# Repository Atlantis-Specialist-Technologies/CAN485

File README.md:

# CAN485
Repository for the Sparkfun AST-CAN485 Development Board

[*Sparkfun AST CAN485 Development Board*](https://www.sparkfun.com/products/14483 "CAN485 on Sparkfun")

# Repository Contents
Repository for the CAN485 Board

* **/Libraries** - Libraries
* **/Examples** - Example code
* **/Documentation** - Documentation
* **/Firmware** - Arduino boards source
* **/Hardware** - Eagle design files

# Documentation
* **/Hookup Guide** - [Hookup guide](https://learn.sparkfun.com/tutorials/ast-can485-hookup-guide) for the CAN485. This contains everything needed to get up and running.

# Licensing
This product is open source.

Refer to LICENSE.md for license information

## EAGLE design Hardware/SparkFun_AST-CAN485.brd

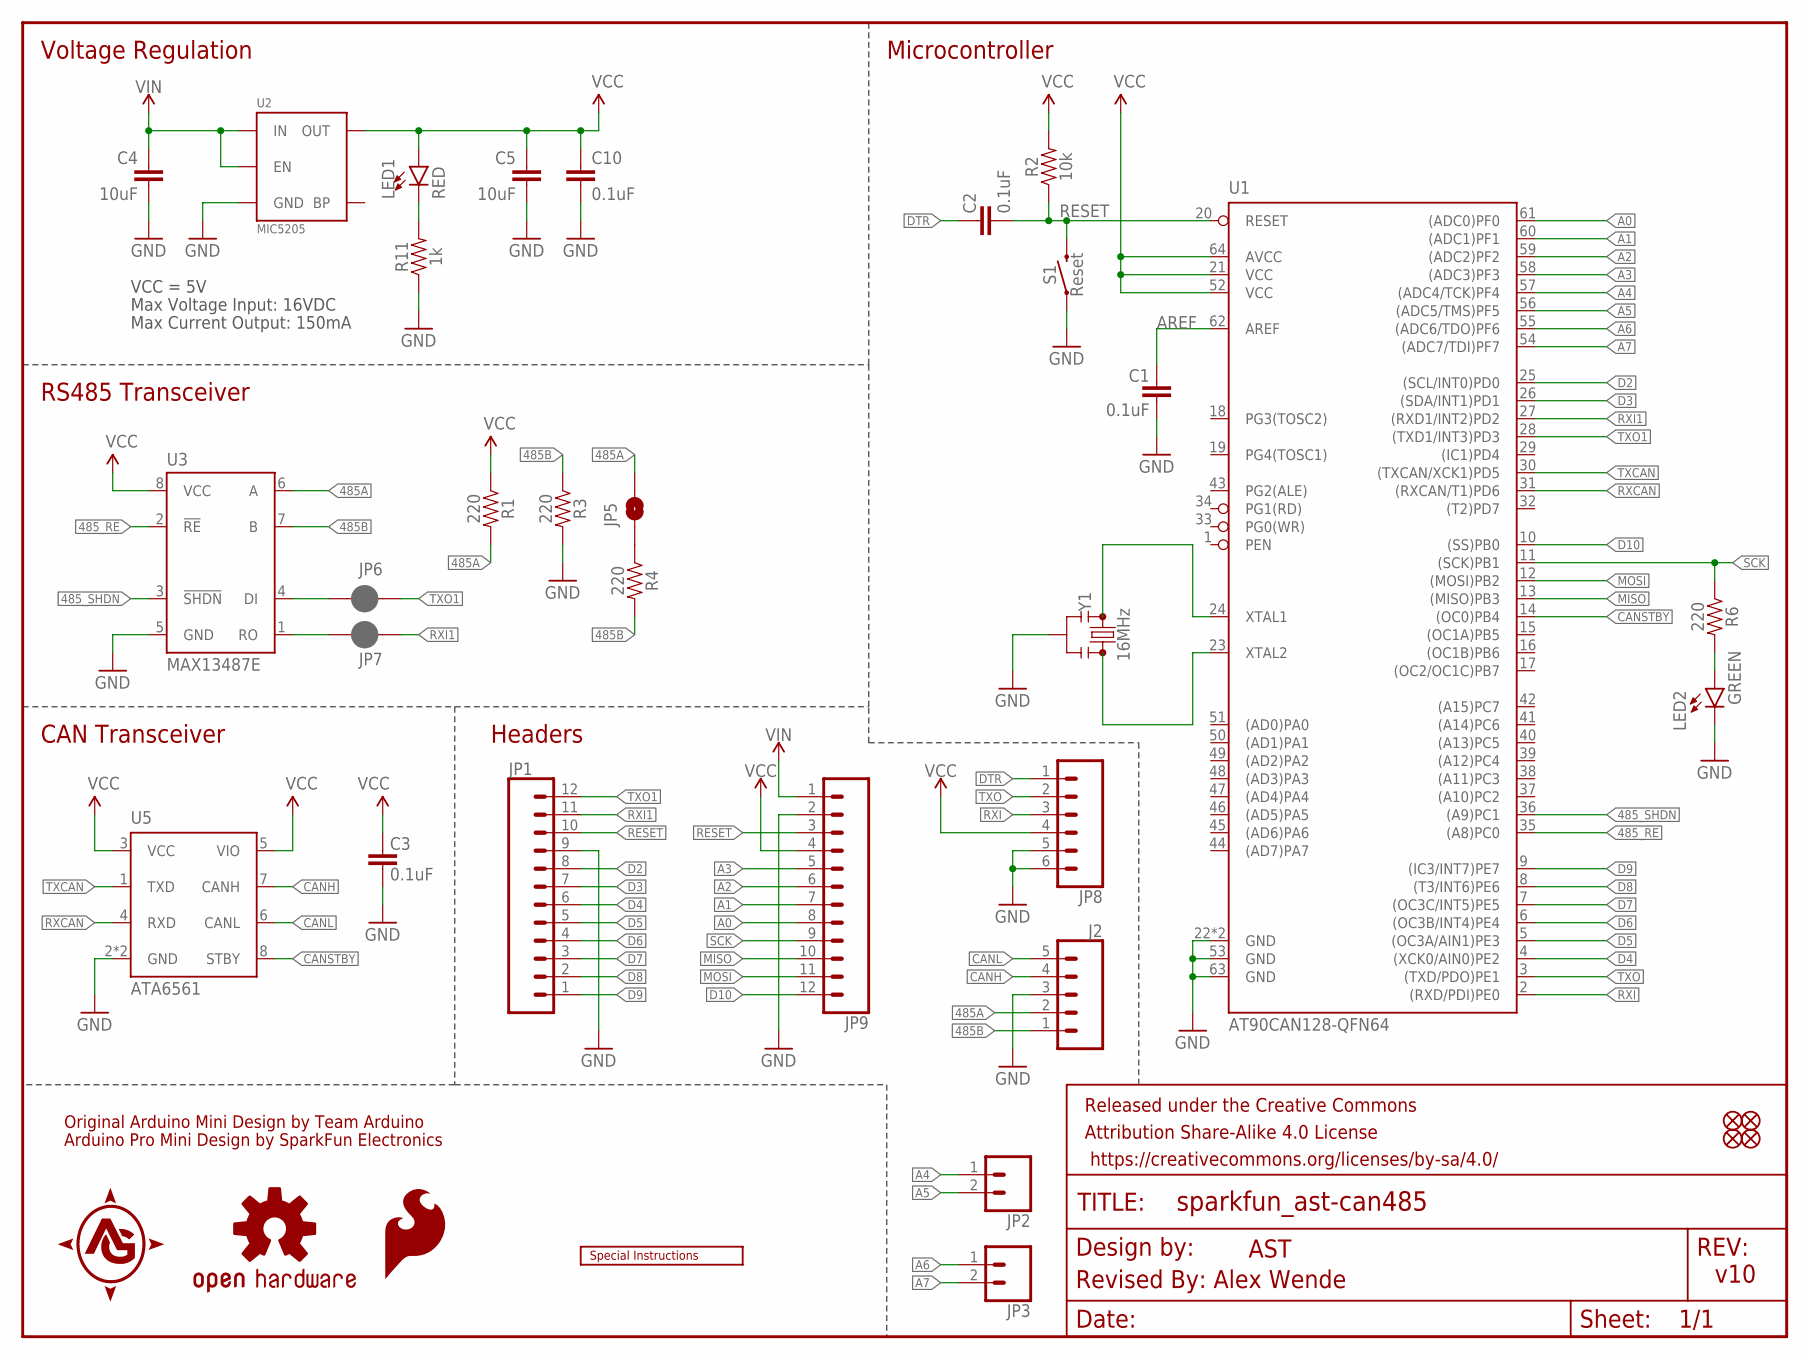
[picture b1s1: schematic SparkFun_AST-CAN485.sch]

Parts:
C1, C2, C3, C10: 0.1uF; 0402
C4, C5: 10uF; 1210
FD1, FD2, FD3, FD4: FIDUCIALUFIDUCIAL; FIDUCIAL-MICRO
FRAME1: FRAME-LETTER; CREATIVE_COMMONS
J2: CONN_05NO_SILK; 1X05_NO_SILK
JP1, JP9: CONN_12NO_SILK; 1X12_NO_SILK
JP2, JP3: CONN_021X02_NO_SILK; 1X02_NO_SILK
JP5: JUMPER-PAD-2-NO; PAD-JUMPER-2-NO_NO_SILK
JP6, JP7: JUMPER-SMT_2_NC_PASTE_NO-SILK; SMT-JUMPER_2_NC_PASTE_NO-SILK
JP8: CONN_06NO_SILK_NO_POP; 1X06_NO_SILK
LED1: RED; LED-0603
LED2: GREEN; LED-0603
LOGO1: OSHW-LOGOMINI; OSHW-LOGO-MINI
LOGO2: SFE_LOGO_FLAME0.05_INCH; SFE_LOGO_FLAME_.05
R1, R3, R4, R6: 220; 0603
R2: 10k; 0603
R11: 1k; 0603
S1: Reset; TACTILE_SWITCH_SMD_4.6X2.8MM
U1: AT90CAN128-QFN64; QFN-64
U2: MIC5205; SOT23-5
U3: MAX13487E; SO08
U5: ATA6561; DFN8
U$1: SPECIAL_INSTRUCTIONS-ORDERING; ORDERING_INSTRUCTIONS
Y1: 16MHz; RESONATOR-SMD-3.2X1.3(SLIM)

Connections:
485A: J2.2, JP5.2, R1.2, U3.6 (A)
485B: J2.1, R3.1, R4.2, U3.7 (B)
485_RE: U1.35 ((A8)PC0), U3.2 (!RE)
485_SHDN: U1.36 ((A9)PC1), U3.3 (!SHDN)
A0: JP9.8, U1.61 ((ADC0)PF0)
A1: JP9.7, U1.60 ((ADC1)PF1)
A2: JP9.6, U1.59 ((ADC2)PF2)
A3: JP9.5, U1.58 ((ADC3)PF3)
A4: JP2.1, U1.57 ((ADC4/TCK)PF4)
A5: JP2.2, U1.56 ((ADC5/TMS)PF5)
A6: JP3.1, U1.55 ((ADC6/TDO)PF6)
A7: JP3.2, U1.54 ((ADC7/TDI)PF7)
AREF: C1.2, U1.62 (AREF)
CANH: J2.4, U5.7 (CANH)
CANL: J2.5, U5.6 (CANL)
CANSTBY: U1.14 ((OC0)PB4), U5.8 (STBY)
D2: JP1.8, U1.25 ((SCL/INT0)PD0)
D3: JP1.7, U1.26 ((SDA/INT1)PD1)
D4: JP1.6, U1.4 ((XCK0/AIN0)PE2)
D5: JP1.5, U1.5 ((OC3A/AIN1)PE3)
D6: JP1.4, U1.6 ((OC3B/INT4)PE4)
D7: JP1.3, U1.7 ((OC3C/INT5)PE5)
D8: JP1.2, U1.8 ((T3/INT6)PE6)
D9: JP1.1, U1.9 ((IC3/INT7)PE7)
D10: JP9.12, U1.10 ((SS)PB0)
DTR: C2.2, JP8.1
GND: C1.1, C3.1, C4.2, C5.2, C10.2, J2.3, JP1.9, JP8.5, JP8.6, JP9.2, LED2.C, R3.2, R11.1, S1.1, S1.2 (1), U1.22 (GND), U1.53 (GND), U1.63 (GND), U1.65 (GND), U2.2 (GND), U3.5 (GND), U5.2 (GND), U5.9 (GND), Y1.2
MISO: JP9.10, U1.13 ((MISO)PB3)
MOSI: JP9.11, U1.12 ((MOSI)PB2)
unnamed: U1.23 (XTAL2), Y1.3
unnamed: U1.24 (XTAL1), Y1.1
unnamed: JP5.1, R4.1
unnamed: LED1.C, R11.2
unnamed: JP6.2, U3.4 (DI)
unnamed: JP7.2, U3.1 (RO)
unnamed: LED2.A, R6.2
RESET: C2.1, JP1.10, JP9.3, R2.1, S1.3 (2), S1.4 (2), U1.20 (RESET)
RXCAN: U1.31 ((RXCAN/T1)PD6), U5.4 (RXD)
RXI: JP8.3, U1.2 ((RXD/PDI)PE0)
RXI1: JP1.11, JP7.1, U1.27 ((RXD1/INT2)PD2)
SCK: JP9.9, R6.1, U1.11 ((SCK)PB1)
TXCAN: U1.30 ((TXCAN/XCK1)PD5), U5.1 (TXD)
TXO: JP8.2, U1.3 ((TXD/PDO)PE1)
TXO1: JP1.12, JP6.1, U1.28 ((TXD1/INT3)PD3)
VCC: C3.2, C5.1, C10.1, JP8.4, JP9.4, LED1.A, R1.1, R2.2, U1.21 (VCC), U1.52 (VCC), U1.64 (AVCC), U2.5 (OUT), U3.8 (VCC), U5.3 (VCC), U5.5 (VIO)
VIN: C4.1, JP9.1, U2.1 (IN), U2.3 (EN)

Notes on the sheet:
Original Arduino Mini Design by Team Arduino
Arduino Pro Mini Design by SparkFun Electronics
Max Voltage Input: 16VDC
Max Current Output: 150mA
VCC = 5V
Voltage Regulation
Microcontroller
RS485 Transceiver
CAN Transceiver
Headers
AST
Revised By: Alex Wende
v10

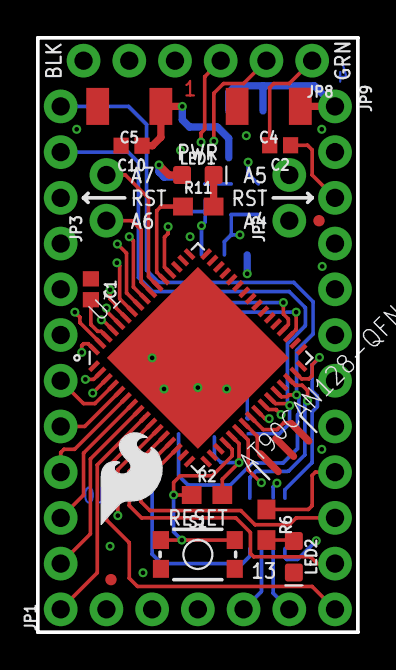
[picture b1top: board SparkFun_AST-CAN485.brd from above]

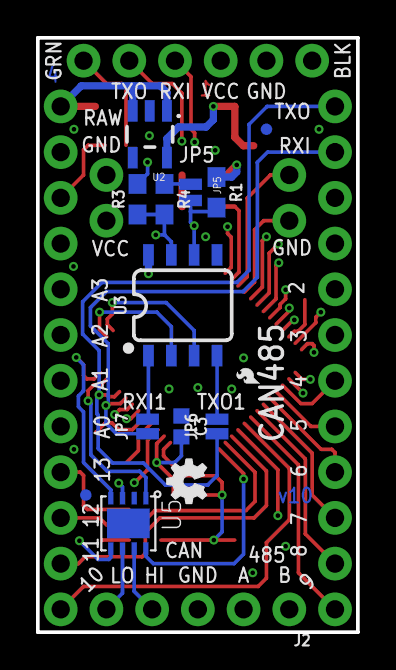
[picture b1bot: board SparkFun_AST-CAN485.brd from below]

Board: 4 copper layers, 17.8 x 33.0 mm, 38 parts (15 on the bottom side), 46 nets.

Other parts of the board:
LOGO3: SFE_LOGO_FLAME0.05_INCH; SFE_LOGO_FLAME_.2

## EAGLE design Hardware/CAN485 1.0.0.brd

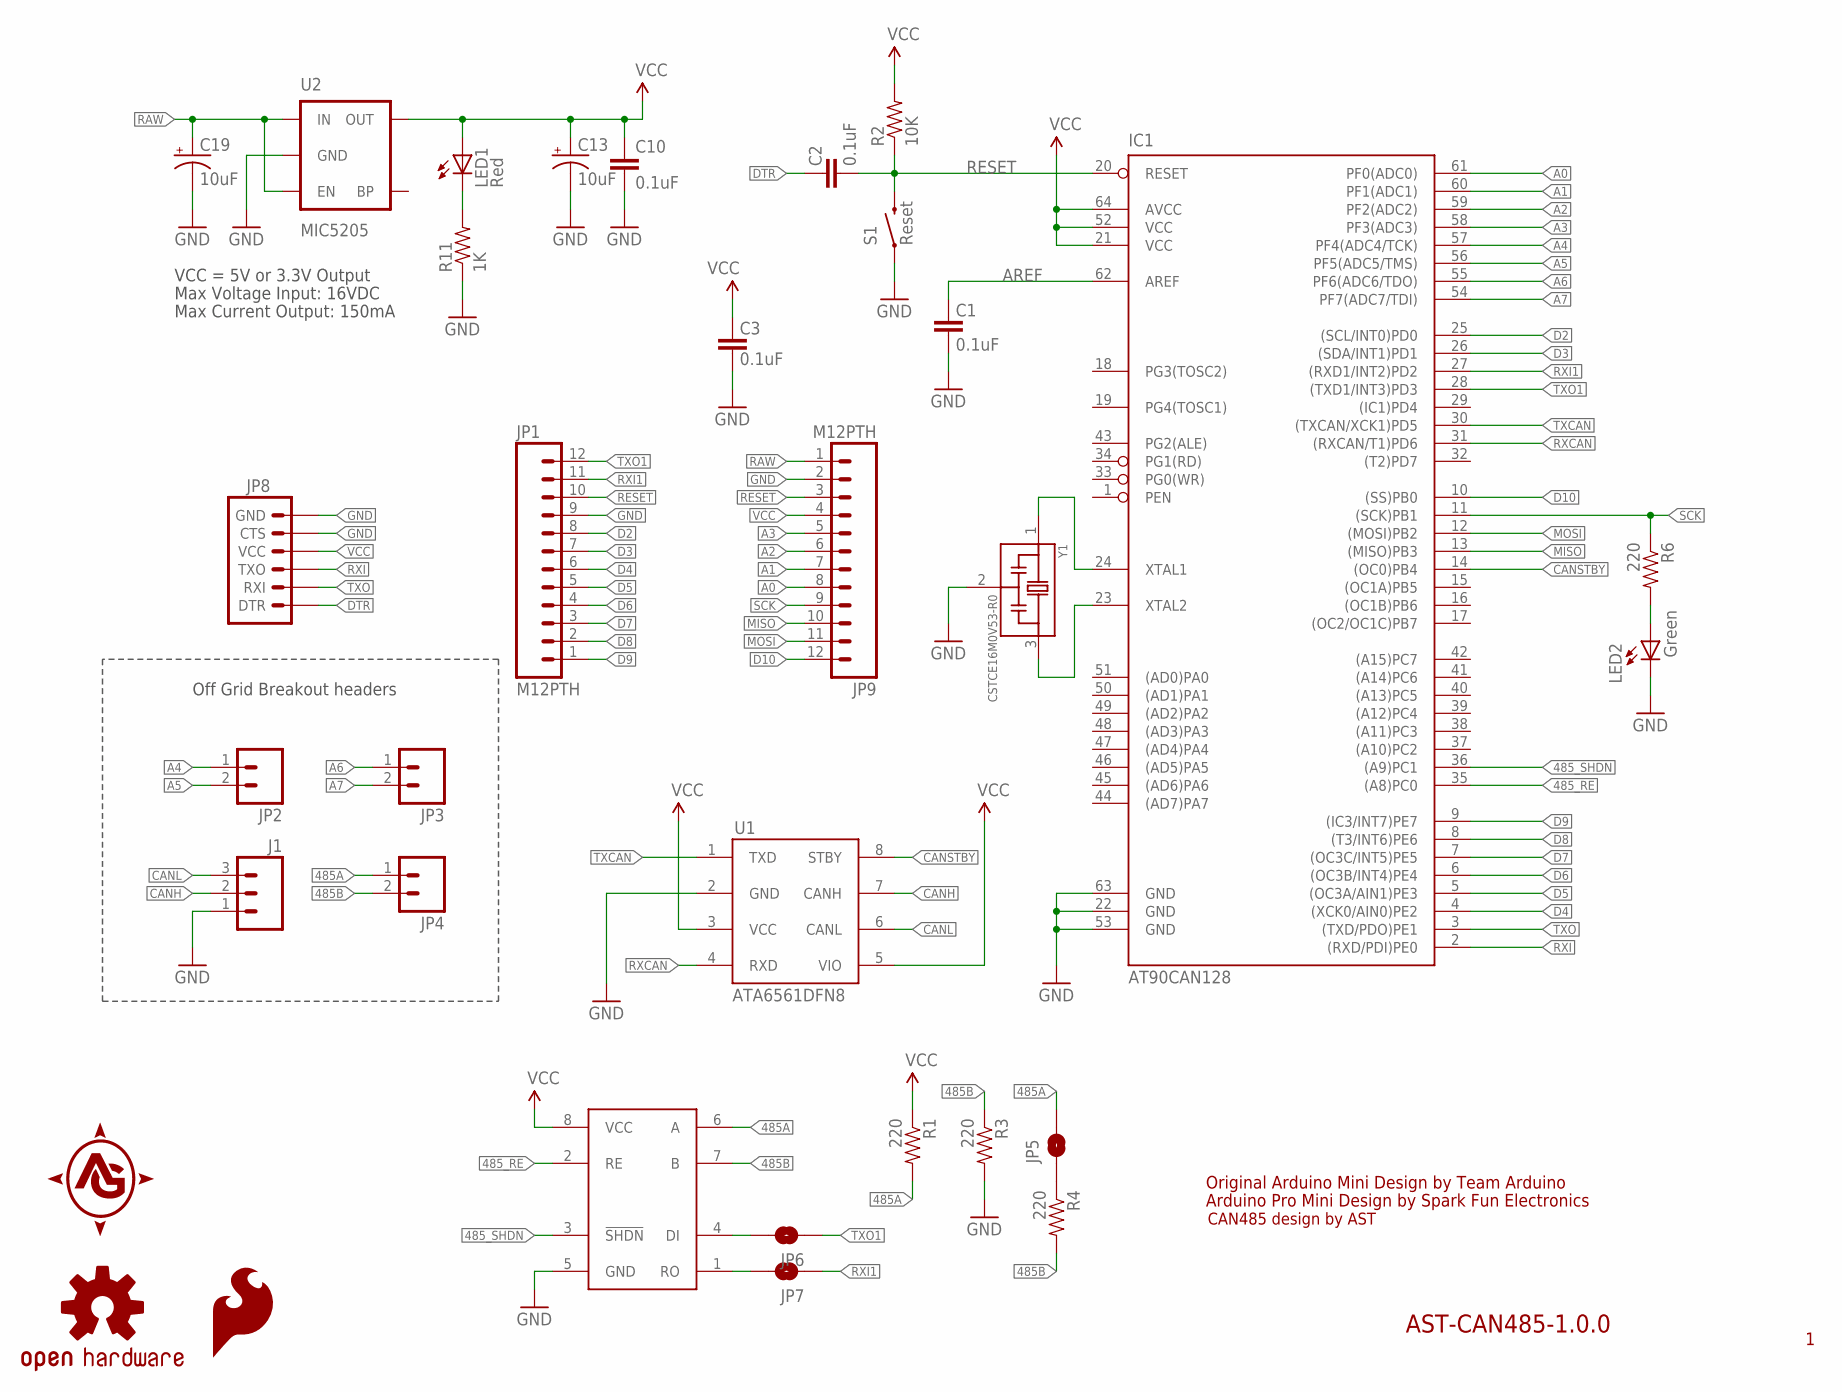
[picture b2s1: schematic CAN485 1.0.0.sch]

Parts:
C1, C2, C3, C10: 0.1uF; 0402-CAP
C13, C19: 10uF; EIA3216
IC1: AT90CAN128; MLF64
J1: M03PTH; 1X03
JP1, JP9: M12PTH; 1X12
JP2, JP3, JP4: M02PTH; 1X02
JP5, JP6, JP7: JUMPER-PAD-2-NO; PAD-JUMPER-2-NO_NO_SILK
JP8: ARDUINO_SERIAL_PROGRAMPTH; 1X06
LED1: Red; 0603-LED-ALT1
LED2: Green; 0603-LED-ALT1
LOGO1: OSHW-LOGOMINI; OSHW-LOGO-MINI
LOGO2: SFE_LOGO_FLAME0.05_INCH; SFE_LOGO_FLAME_.05
R1, R3, R4, R6: 220; 0402-RES
R2: 10K; 0402-RES
R11: 1K; 0402-RES
S1: Reset; TACTILE-SWITCH-1101NE
U1: ATA6561DFN8; MSOP8
U2: MIC5205; SC70
U4: MAX13487SOIC; MAX13487
Y1: CSTCE16M0V53-R0; OSC_CSTCE16M0V53-R0

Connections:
485A: JP4.1, JP5.2, R1.2, U4.6 (A)
485B: JP4.2, R3.1, R4.2, U4.7 (B)
485_RE: IC1.35 ((A8)PC0), U4.2 (RE)
485_SHDN: IC1.36 ((A9)PC1), U4.3 (!SHDN)
A0: IC1.61 (PF0(ADC0)), JP9.8
A1: IC1.60 (PF1(ADC1)), JP9.7
A2: IC1.59 (PF2(ADC2)), JP9.6
A3: IC1.58 (PF3(ADC3)), JP9.5
A4: IC1.57 (PF4(ADC4/TCK)), JP2.1
A5: IC1.56 (PF5(ADC5/TMS)), JP2.2
A6: IC1.55 (PF6(ADC6/TDO)), JP3.1
A7: IC1.54 (PF7(ADC7/TDI)), JP3.2
AREF: C1.2, IC1.62 (AREF)
CANH: J1.2, U1.7 (CANH)
CANL: J1.3, U1.6 (CANL)
CANSTBY: IC1.14 ((OC0)PB4), U1.8 (STBY)
D2: IC1.25 ((SCL/INT0)PD0), JP1.8
D3: IC1.26 ((SDA/INT1)PD1), JP1.7
D4: IC1.4 ((XCK0/AIN0)PE2), JP1.6
D5: IC1.5 ((OC3A/AIN1)PE3), JP1.5
D6: IC1.6 ((OC3B/INT4)PE4), JP1.4
D7: IC1.7 ((OC3C/INT5)PE5), JP1.3
D8: IC1.8 ((T3/INT6)PE6), JP1.2
D9: IC1.9 ((IC3/INT7)PE7), JP1.1
D10: IC1.10 ((SS)PB0), JP9.12
DTR: C2.2, JP8.1 (DTR)
GND: C1.1, C3.1, C10.2, C13.C (-), C19.C (-), IC1.22 (GND), IC1.53 (GND), IC1.63 (GND), J1.1, JP1.9, JP8.5 (CTS), JP8.6 (GND), JP9.2, LED2.C, R3.2, R11.1, S1.P$1 (1), U1.2 (GND), U2.2 (GND), U4.5 (GND), Y1.2
MISO: IC1.13 ((MISO)PB3), JP9.10
MOSI: IC1.12 ((MOSI)PB2), JP9.11
unnamed: IC1.23 (XTAL2), Y1.3
unnamed: IC1.24 (XTAL1), Y1.1
unnamed: JP5.1, R4.1
unnamed: LED1.C, R11.2
unnamed: JP6.2, U4.4 (DI)
unnamed: JP7.2, U4.1 (RO)
unnamed: LED2.A, R6.2
RAW: C19.A (+), JP9.1, U2.1 (IN), U2.3 (EN)
RESET: C2.1, IC1.20 (RESET), JP1.10, JP9.3, R2.1, S1.P$2 (2)
RXCAN: IC1.31 ((RXCAN/T1)PD6), U1.4 (RXD)
RXI: IC1.2 ((RXD/PDI)PE0), JP8.3 (TXO)
RXI1: IC1.27 ((RXD1/INT2)PD2), JP1.11, JP7.1
SCK: IC1.11 ((SCK)PB1), JP9.9, R6.1
TXCAN: IC1.30 ((TXCAN/XCK1)PD5), U1.1 (TXD)
TXO: IC1.3 ((TXD/PDO)PE1), JP8.2 (RXI)
TXO1: IC1.28 ((TXD1/INT3)PD3), JP1.12, JP6.1
VCC: C3.2, C10.1, C13.A (+), IC1.21 (VCC), IC1.52 (VCC), IC1.64 (AVCC), JP8.4 (VCC), JP9.4, LED1.A, R1.1, R2.2, U1.3 (VCC), U1.5 (VIO), U2.5 (OUT), U4.8 (VCC)

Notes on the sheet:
Original Arduino Mini Design by Team Arduino
Arduino Pro Mini Design by Spark Fun Electronics
Max Voltage Input: 16VDC
Max Current Output: 150mA
VCC = 5V or 3.3V Output
Off Grid Breakout headers
CAN485 design by AST
AST-CAN485-1.0.0

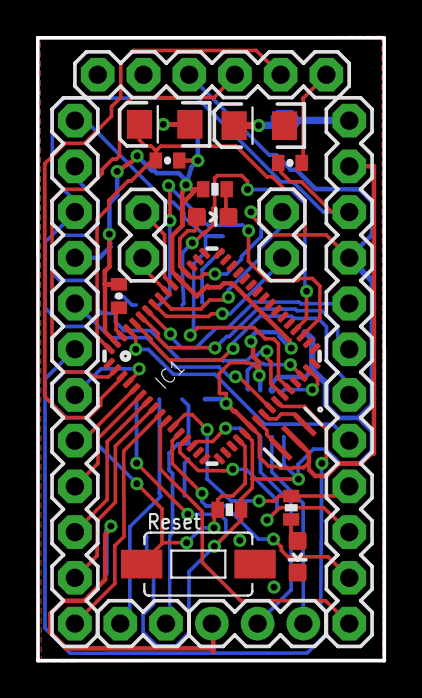
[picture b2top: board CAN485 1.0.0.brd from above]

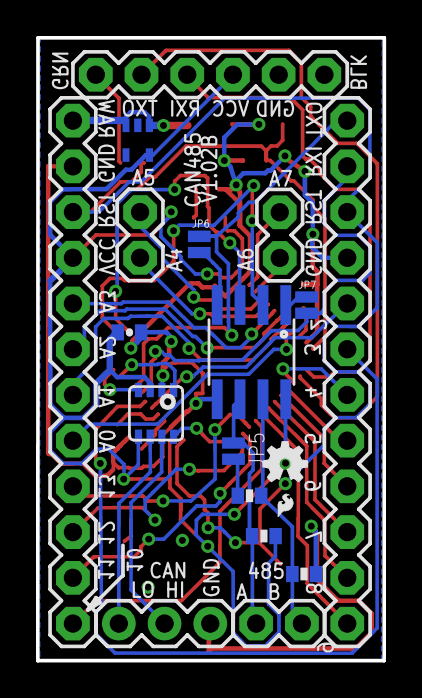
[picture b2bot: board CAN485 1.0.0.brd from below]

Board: 2 copper layers, 19.2 x 34.6 mm, 32 parts (12 on the bottom side), 46 nets.

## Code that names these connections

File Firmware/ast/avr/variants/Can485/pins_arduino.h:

/*
  pins_arduino.h - Pin definition functions for Arduino
  Part of Arduino - http://www.arduino.cc/

  Copyright (c) 2007 David A. Mellis

  This library is free software; you can redistribute it and/or
  modify it under the terms of the GNU Lesser General Public
  License as published by the Free Software Foundation; either
  version 2.1 of the License, or (at your option) any later version.

  This library is distributed in the hope that it will be useful,
  but WITHOUT ANY WARRANTY; without even the implied warranty of
  MERCHANTABILITY or FITNESS FOR A PARTICULAR PURPOSE.  See the GNU
  Lesser General Public License for more details.

  You should have received a copy of the GNU Lesser General
  Public License along with this library; if not, write to the
  Free Software Foundation, Inc., 59 Temple Place, Suite 330,
  Boston, MA  02111-1307  USA
*/

/*
  Modified by Atlantis Specialist Technologies
  by James Blakey-Milner, 1 Aug 2017.
  Added support for the AST CAN485 board
  Note! AST modifications are in early development (alpha)
  and are likely to change without notice.
*/

#ifndef Pins_Arduino_h
#define Pins_Arduino_h

#include <avr/pgmspace.h>

#define NUM_DIGITAL_PINS            24
#define NUM_ANALOG_INPUTS           8
#define analogInputToDigitalPin(p)  ((p < 8) ? (p) + 14 : -1)


#define digitalPinHasPWM(p)         (((p) == 5 || (p) == 6 || (p) == 7 )


#define PIN_SPI_SS    (10)
#define PIN_SPI_MOSI  (11)
#define PIN_SPI_MISO  (12)
#define PIN_SPI_SCK   (13)

static const uint8_t SS   = PIN_SPI_SS;
static const uint8_t MOSI = PIN_SPI_MOSI;
static const uint8_t MISO = PIN_SPI_MISO;
static const uint8_t SCK  = PIN_SPI_SCK;

#define PIN_WIRE_SDA        (3)
#define PIN_WIRE_SCL        (2)

static const uint8_t SDA = PIN_WIRE_SDA;
static const uint8_t SCL = PIN_WIRE_SCL;

#define LED_BUILTIN 13

#define PIN_A0   (14)
#define PIN_A1   (15)
#define PIN_A2   (16)
#define PIN_A3   (17)
#define PIN_A4   (18)
#define PIN_A5   (19)
#define PIN_A6   (20)
#define PIN_A7   (21)

static const uint8_t A0 = PIN_A0;
static const uint8_t A1 = PIN_A1;
static const uint8_t A2 = PIN_A2;
static const uint8_t A3 = PIN_A3;
static const uint8_t A4 = PIN_A4;
static const uint8_t A5 = PIN_A5;
static const uint8_t A6 = PIN_A6;
static const uint8_t A7 = PIN_A7;

// pin change interrupts not supported
#define digitalPinToPCICR(p)    ((uint8_t *)0)
#define digitalPinToPCICRbit(p) (NO_PIN_CHANGE_INTERRUPT)
#define digitalPinToPCMSK(p)    ((uint8_t *)0)
#define digitalPinToPCMSKbit(p) (NO_PIN_CHANGE_INTERRUPT_MASK)

//#define digitalPinToInterrupt(p)  ((p) == 2 ? 0 : ((p) == 3 ? 1 : NOT_AN_INTERRUPT))
#define digitalPinToInterrupt(p)  (((p) >= 6 && (p) <= 9) ? ((p) - 2) : (((p) == 2) ? 0 : (((p) == 3) ? 1 : NOT_AN_INTERRUPT)))         // AST done

#ifdef ARDUINO_MAIN

// On the Arduino board, digital pins are also used
// for the analog output (software PWM).  Analog input
// pins are a separate set.




// these arrays map port names (e.g. port B) to the
// appropriate addresses for various functions (e.g. reading
// and writing)

/*
 * See Arduino.h for use of these
 * ports start with PA = 1 (not 0)
 */
const uint16_t PROGMEM port_to_mode_PGM[] = {
	NOT_A_PORT,
	NOT_A_PORT,
	(uint16_t) &DDRB,
	(uint16_t) &DDRC,
	(uint16_t) &DDRD,
	(uint16_t) &DDRE,
	(uint16_t) &DDRF,
};

const uint16_t PROGMEM port_to_output_PGM[] = {
	NOT_A_PORT,
	NOT_A_PORT,
	(uint16_t) &PORTB,
	(uint16_t) &PORTC,
	(uint16_t) &PORTD,
	(uint16_t) &PORTE,
	(uint16_t) &PORTF,
};

const uint16_t PROGMEM port_to_input_PGM[] = {
	NOT_A_PORT,
	NOT_A_PORT,
	(uint16_t) &PINB,
	(uint16_t) &PINC,
	(uint16_t) &PIND,
	(uint16_t) &PINE,
	(uint16_t) &PINF,
};

const uint8_t PROGMEM digital_pin_to_port_PGM[] = {
	PE, /*  0 */
	PE, /*  1 */
	PD, /*  2 */
	PD, /*  3 */
	PE, /*  4 */
	PE, /*  5 */
	PE, /*  6 */
	PE, /*  7 */
	PE, /*  8 */
	PE, /*  9 */
	PB, /* 10 */
	PB, /* 11 */
	PB, /* 12 */
	PB, /* 13 */
	PF, /* 14 */
	PF, /* 15 */
	PF, /* 16 */
	PF, /* 17 */
	PF, /* 18 */
	PF, /* 19 */
	PF, /* 20 */
	PF, /* 21 */
	PC, /* 22 */
	PC, /* 23 */
};

const uint8_t PROGMEM digital_pin_to_bit_mask_PGM[] = {
	_BV(1), /*  0, PE1 				*/
	_BV(0), /*  1, PE0 				*/
	_BV(0), /*  2, PD0 				*/
	_BV(1), /*  3, PD1 				*/
	_BV(2), /*  4, PE2 				*/
	_BV(3), /*  5, PE3 				*/
	_BV(4), /*  6, PE4 				*/
	_BV(5), /*  7, PE5 				*/
	_BV(6), /*  8, PE6 				*/
	_BV(7), /*  9, PE7 				*/
	_BV(0), /* 10, PB0 				*/
	_BV(2), /* 11, PB2, MOSI 		*/
	_BV(3), /* 12, PB3, MISO 		*/
	_BV(1), /* 13, PB1, LED_BUILTIN */
	_BV(0), /* 14, PF0 				*/
	_BV(1), /* 15, PF1 				*/
	_BV(2), /* 16, PF2 				*/
	_BV(3), /* 17, PF3 				*/
	_BV(4), /* 18, PF4 				*/
	_BV(5), /* 19, PF5 				*/
	_BV(6), /* 20, PF6 				*/
	_BV(7), /* 21, PF7 				*/
	_BV(0), /* 22, PC0, RS485_RE	*/
	_BV(1), /* 23, PC1, RS485_SHDN	*/
};

const uint8_t PROGMEM digital_pin_to_timer_PGM[] = {
	NOT_ON_TIMER,
	NOT_ON_TIMER,
	NOT_ON_TIMER,
	NOT_ON_TIMER,
	NOT_ON_TIMER,
	TIMER3A, /*       5, PE3 */
	TIMER3B, /*       6, PE4 */
	TIMER3C, /*       7, PE5 */
	NOT_ON_TIMER,
	NOT_ON_TIMER,
	NOT_ON_TIMER,
	NOT_ON_TIMER,
	NOT_ON_TIMER,
	NOT_ON_TIMER,
	NOT_ON_TIMER,
	NOT_ON_TIMER,
	NOT_ON_TIMER,
	NOT_ON_TIMER,
	NOT_ON_TIMER,
	NOT_ON_TIMER,
	NOT_ON_TIMER,
	NOT_ON_TIMER,
	NOT_ON_TIMER,
	NOT_ON_TIMER,
};

#endif

// These serial port names are intended to allow libraries and architecture-neutral
// sketches to automatically default to the correct port name for a particular type
// of use.  For example, a GPS module would normally connect to SERIAL_PORT_HARDWARE_OPEN,
// the first hardware serial port whose RX/TX pins are not dedicated to another use.
//
// SERIAL_PORT_MONITOR        Port which normally prints to the Arduino Serial Monitor
//
// SERIAL_PORT_USBVIRTUAL     Port which is USB virtual serial
//
// SERIAL_PORT_LINUXBRIDGE    Port which connects to a Linux system via Bridge library
//
// SERIAL_PORT_HARDWARE       Hardware serial port, physical RX & TX pins.
//
// SERIAL_PORT_HARDWARE_OPEN  Hardware serial ports which are open for use.  Their RX & TX
//                            pins are NOT connected to anything by default.
#define SERIAL_PORT_MONITOR   Serial
#define SERIAL_PORT_HARDWARE  Serial

#endif

/*
 * http://www.avrfreaks.net/forum/setting-jtd-bit-mcucr
 * include in library
 */
#define jtd_set(x) \
{ \
        __asm__ __volatile__ ( \
                "in __tmp_reg__,__SREG__" "\n\t" \
                "cli" "\n\t" \
                "out %1, %0" "\n\t" \
                "out __SREG__, __tmp_reg__" "\n\t"\
                "out %1, %0" "\n\t" \
                : /* no outputs */ \
                : "r" ((uint8_t)(x ? (1<<JTD) : 0)), \
                  "M" (_SFR_IO_ADDR(MCUCR)) \
                : "r0"); \
}

// RS485 control bits
#define RS485_RE 22
#define RS485_SHDN 23

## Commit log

2017-08-04 restructure. updated readme
2017-08-04 edit readme
2017-08-04 edits
2017-08-04 added examples
2017-08-11 add example
2017-08-11 update redme link
2017-08-11 update example
2017-08-11 examples readme
2017-08-11 update link
2018-01-16 Add examples
2018-01-26 Arduino boards source
2018-01-26 Libraries, Documentation, Hardware
2018-01-26 Libraries
2018-01-26 Update eagle files with Sparkfun revisions
2018-02-12 Settable Baudrate
    Add ability to set baudrate in canInit function. Previously had to modify config.h in the library folder.
2018-02-12 Update Examples
2018-02-21 Baudrate
    Make CAN baudrate settable in the canInit function
2018-03-02 Readme and Licensing
2018-03-02 Readme
2018-03-05 library properties
2018-03-05 Recreate
    Fork from source (was a modified clone before) .
2018-03-05 Add libraries as subtrees
2018-03-05 License
2018-03-05 Readme updates
2018-03-05 Refactor
2018-03-05 Refactor. Readme. Licensing
2018-03-05 Properties. Readme
2018-03-05 remove subtree test
2018-03-05 Update links
2018-03-06 Update JTAG disable example
    Added comment referring to an issue raised. Added blink code to test outputs
2018-03-06 Update comment on JTAG Disable example
2018-12-27 Fix file/directory case for case sensitive filesystems
2020-05-29 Provide menu options for 16, 8, and 4 Mhz
2021-02-16 Update boards.txt
    Fixed case of "can485"

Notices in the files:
parts and their libraries:
SparkFun-Connectors: Licensing: Creative Commons ShareAlike 4.0 International - https://creativecommons.org/licenses/by-sa/4.0
SparkFun-Aesthetics: Released under the Creative Commons Attribution Share-Alike 4.0 License
SparkFun-Aesthetics: https://creativecommons.org/licenses/by-sa/4.0
